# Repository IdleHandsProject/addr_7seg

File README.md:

# Addressable 7-Segment Displays
An API that lets you display numbers and letters on Addr7Segment LED displays that are available 
from [PCBway](https://www.pcbway.com/project/shareproject/Addressable_7_Segment_Display.html)
This board uses 3 x WS2811 IC to control the segments of the segmented display. 
This means they can be daisy chained and controlled with just a single data line. 

You can find the Open Source hardware PCB design and Gerber files [here](https://github.com/IdleHandsProject/addr_7seg)

## Installing and Use
The downloaded code should be added to your arduino IDE libraries folder, and the library requires the [Adafruit NeoPixel library](https://github.com/adafruit/Adafruit_NeoPixel) for it to function.

To include the Addr7Segment library in your project:

    #include <Addr7Segment.h>

You can then initialise the display with the following line that includes the number of Neo7Segment digits and the GPIO to control them:

	#define DIGITS       5   // Number of digits
	#define PIN          4   // Pin number

	// Initalise the display with 5 Addr7Segment boards connected to GPIO 4
	Addr7Segment disp( DIGITS, PIN );

You then start the display with the begin method, passing the brightness [0%-100%]:

    disp.Begin(20);

The you simply pass the display the String you would like displayed and a brigtness [0%-100%]:

    disp.DisplayText( "1234", 20 );

## Check out the video! - Click the Image

Order the PCB from PCBWay Here: http://bit.ly/addr7segpcb

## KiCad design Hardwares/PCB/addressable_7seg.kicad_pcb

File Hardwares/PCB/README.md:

# TEMPLATE KICAD PROJECT
## Sean Hodgins

If you're reading this, it means I have started a new project but have neglected to update the README file.
Please notify me of this by any means possible. 

Twitter: @idlehandsdev
Instagram: @idlehandsdev

Since you're reading this, go check out my YouTube Channel! http://youtube.com/seanhodginsfilms

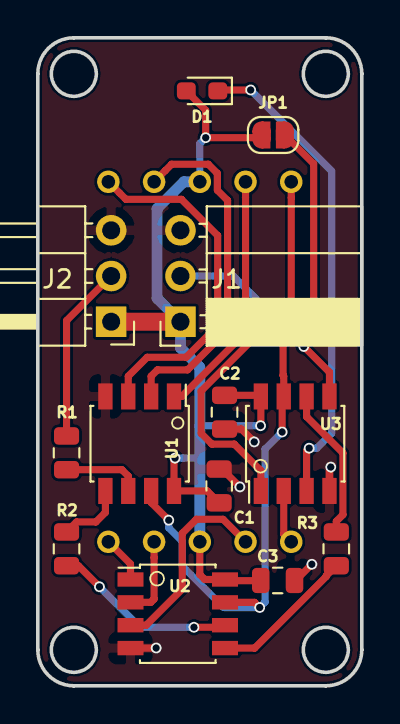
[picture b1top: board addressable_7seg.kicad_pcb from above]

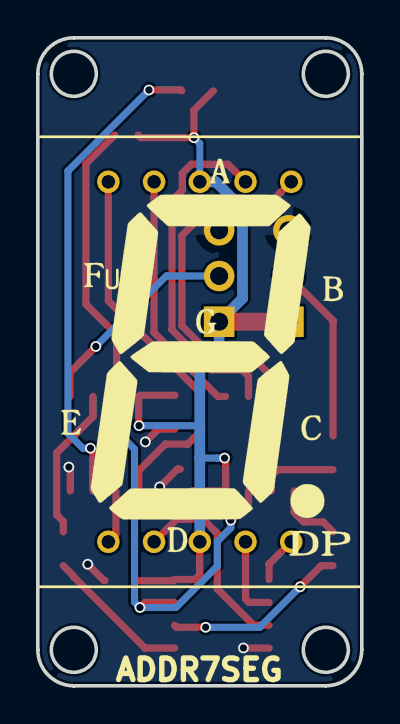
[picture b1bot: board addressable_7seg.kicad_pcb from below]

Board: 2 copper layers, 18.0 x 36.0 mm, 15 parts (2 on the bottom side), 19 nets.

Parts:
C1, C2, C3: 1uF; C_0805_2012Metric
D1: LED; LED_0603_1608Metric_Pad1.05x0.95mm_HandSolder
J1: OUT; PinSocket_1x03_P2.54mm_Horizontal
J2: IN; PinHeader_1x03_P2.54mm_Horizontal
JP1: Jumper_NC_Small; SolderJumper-2_P1.3mm_Open_RoundedPad1.0x1.5mm
R1, R2, R3: 33R; R_0805_2012Metric
SEVENSEG: SEVENSEG; sevenseg
U1, U2, U3: WS2811; SSOP-8_3.95x5.21x3.27mm_P1.27mm
U4: KCSA02-107; YSD-160AR4B-8

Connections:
A: U1.2, U4.7
B: U1.3, U4.6
C: U2.2, U4.4
D: U2.3, U4.2
DP: U2.1, U4.5
E: U3.2, U4.1
F: U1.1, U4.9
G: U3.1, U4.10
GND: C1.2, C2.2, C3.2, J1.3, J2.3, U1.4, U2.4, U3.4
IN: J2.2, R1.2
unnamed: D1.1, U3.3
unnamed: R1.1, U1.6
unnamed: R2.1, U1.5
unnamed: R2.2, U2.6
unnamed: R3.1, U2.5
unnamed: R3.2, U3.6
OUT: J1.2, U3.5
SET: JP1.2, U1.7, U2.7, U3.7
VCC: C1.1, C2.1, C3.1, D1.2, J1.1, J2.1, JP1.1, U1.8, U2.8, U3.8, U4.3, U4.8

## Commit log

2019-01-07 updated ignore file
2019-01-07 added demo program
2019-01-08 updated notes
2019-01-08 added links
2019-01-09 add lib
2019-01-09 New library created
    Library is currently untested...
2019-04-05 small changes and firmware
2019-04-05 fixes for display leds
